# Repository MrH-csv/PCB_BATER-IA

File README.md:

# BATER-IA_PCB
Kicad files for the PCB design.

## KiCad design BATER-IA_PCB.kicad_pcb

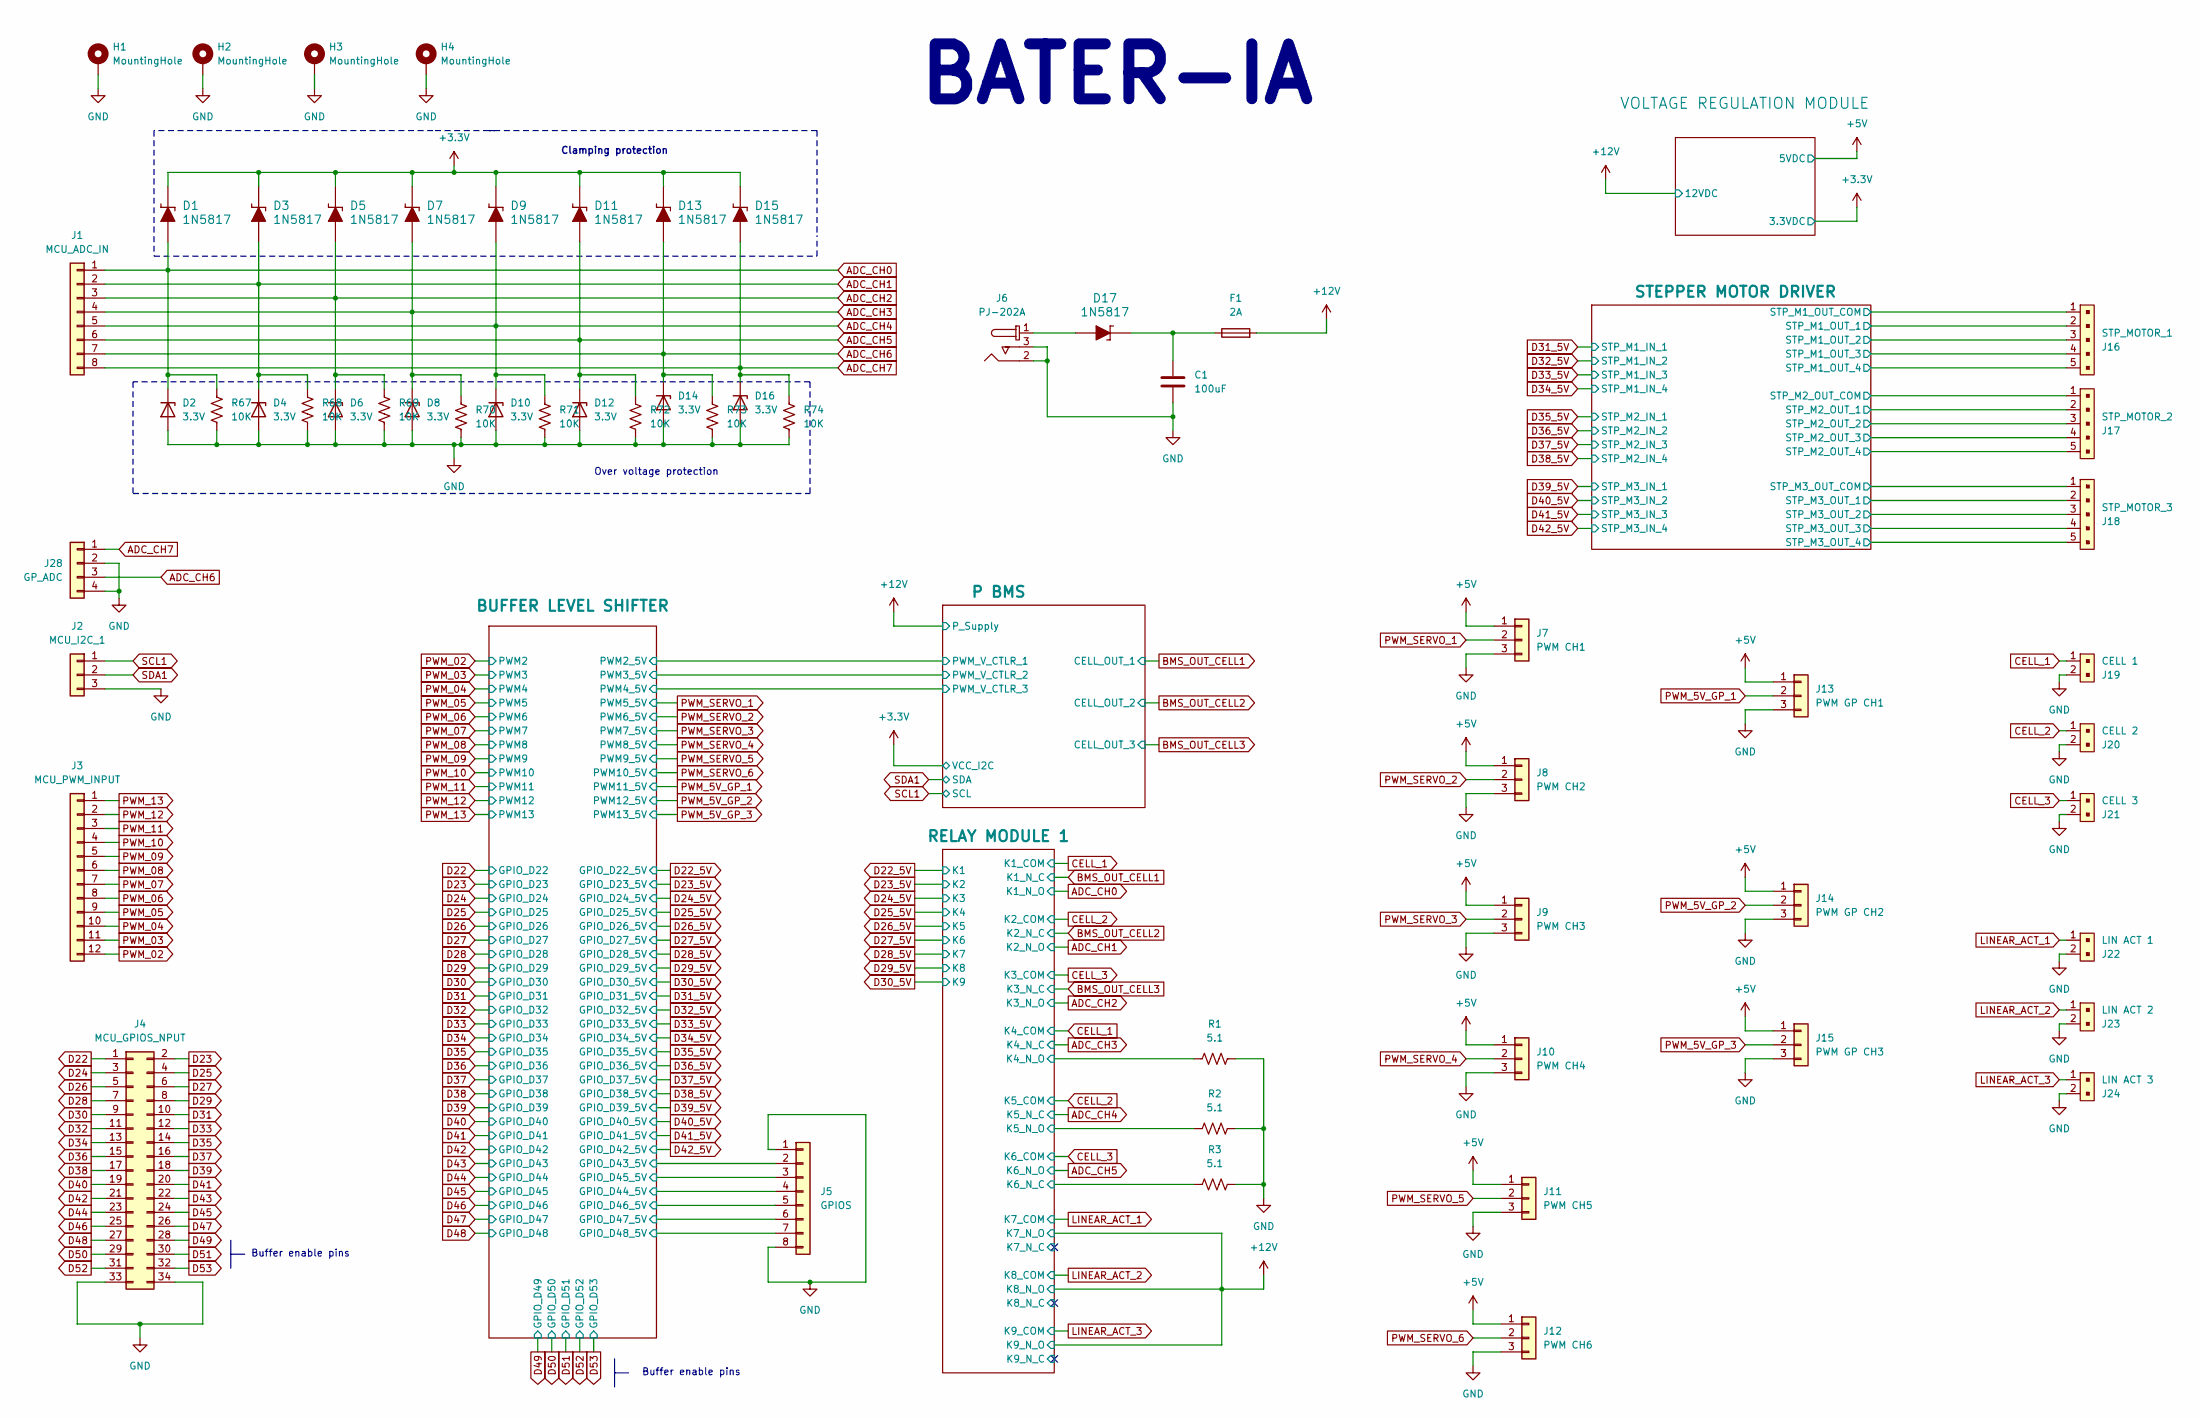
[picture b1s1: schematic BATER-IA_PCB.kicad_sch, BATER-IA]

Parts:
C1: 100uF; CP_Radial_D8.0mm_P5.00mm
D1, D3, D5, D7, D9, D11, D13, D15, D17: 1N5817; D_DO-41_SOD81_P9.20mm_Horizontal; MPN 1N5819; Digi-Key_PN 1N5819FSCT-ND
D2, D4, D6, D8, D10, D12, D14, D16: 3.3V; D_DO-35_SOD27_P10.16mm_Horizontal
F1: 2A; Fuseholder_Clip-5x20mm_Bel_FC-203-22_Lateral_P17.80x5.00mm_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
H1, H2, H3, H4: MountingHole; MountingHole_2.2mm_M2_DIN965_Pad_TopBottom
J1: MCU_ADC_IN; PinHeader_1x08_P2.54mm_Vertical
J2: MCU_I2C_1; PinHeader_1x03_P2.54mm_Vertical
J3: MCU_PWM_INPUT; PinHeader_1x12_P2.54mm_Vertical
J4: MCU_GPIOS_NPUT; PinHeader_2x17_P2.54mm_Vertical
J5: GPIOS; PinHeader_1x08_P2.54mm_Vertical
J6: PJ-202A; BarrelJack_Horizontal; MPN PJ-202A; Digi-Key_PN CP-202A-ND
J7: PWM CH1; PinHeader_1x03_P2.54mm_Vertical
J8: PWM CH2; PinHeader_1x03_P2.54mm_Vertical
J9: PWM CH3; PinHeader_1x03_P2.54mm_Vertical
J10: PWM CH4; PinHeader_1x03_P2.54mm_Vertical
J11: PWM CH5; PinHeader_1x03_P2.54mm_Vertical
J12: PWM CH6; PinHeader_1x03_P2.54mm_Vertical
J13: PWM GP CH1; PinHeader_1x03_P2.54mm_Vertical
J14: PWM GP CH2; PinHeader_1x03_P2.54mm_Vertical
J15: PWM GP CH3; PinHeader_1x03_P2.54mm_Vertical
J16: STP_MOTOR_1; PinHeader_1x5_P2.5mm_Drill1.1mm; MPN B5B-XH-A(LF)(SN); Digi-Key_PN 455-2270-ND
J17: STP_MOTOR_2; PinHeader_1x5_P2.5mm_Drill1.1mm; MPN B5B-XH-A(LF)(SN); Digi-Key_PN 455-2270-ND
J18: STP_MOTOR_3; PinHeader_1x5_P2.5mm_Drill1.1mm; MPN B5B-XH-A(LF)(SN); Digi-Key_PN 455-2270-ND
J19: CELL 1; PinHeader_1x2_P2.5mm_Drill1.1mm; MPN B2B-XH-A(LF)(SN); Digi-Key_PN 455-2247-ND
J20: CELL 2; PinHeader_1x2_P2.5mm_Drill1.1mm; MPN B2B-XH-A(LF)(SN); Digi-Key_PN 455-2247-ND
J21: CELL 3; PinHeader_1x2_P2.5mm_Drill1.1mm; MPN B2B-XH-A(LF)(SN); Digi-Key_PN 455-2247-ND
J22: LIN ACT 1; PinHeader_1x2_P2.5mm_Drill1.1mm; MPN B2B-XH-A(LF)(SN); Digi-Key_PN 455-2247-ND
J23: LIN ACT 2; PinHeader_1x2_P2.5mm_Drill1.1mm; MPN B2B-XH-A(LF)(SN); Digi-Key_PN 455-2247-ND
J24: LIN ACT 3; PinHeader_1x2_P2.5mm_Drill1.1mm; MPN B2B-XH-A(LF)(SN); Digi-Key_PN 455-2247-ND
J28: GP_ADC; PinHeader_1x04_P2.54mm_Vertical
R1, R2, R3: 5.1; R_Axial_DIN0614_L14.3mm_D5.7mm_P15.24mm_Horizontal
R67, R68, R69, R70, R71, R72, R73, R74: 10K; R_Axial_DIN0207_L6.3mm_D2.5mm_P7.62mm_Horizontal

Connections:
+3.3V: D1.K, D3.K, D5.K, D7.K, D9.K, D11.K, D13.K, D15.K; also elsewhere on the board
+5V: J7.1, J8.1, J9.1, J10.1, J11.1, J12.1, J13.1, J14.1, J15.1, J16.1, J17.1, J18.1; also elsewhere on the board
+12V: F1.2; also elsewhere on the board
/BUFFER LEVEL SHIFTER/GPIO_D43_5V: J5.2; also elsewhere on the board
/BUFFER LEVEL SHIFTER/GPIO_D44_5V: J5.4; also elsewhere on the board
/BUFFER LEVEL SHIFTER/GPIO_D45_5V: J5.3; also elsewhere on the board
/BUFFER LEVEL SHIFTER/GPIO_D46_5V: J5.5; also elsewhere on the board
/BUFFER LEVEL SHIFTER/GPIO_D47_5V: J5.6; also elsewhere on the board
/BUFFER LEVEL SHIFTER/GPIO_D48_5V: J5.7; also elsewhere on the board
/RELAY MODULE 1/K4_N_O: R1.1; also elsewhere on the board
/RELAY MODULE 1/K5_N_O: R2.1; also elsewhere on the board
/RELAY MODULE 1/K6_N_C: R3.1; also elsewhere on the board
/STEPPER MOTOR DRIVER/STP_M1_OUT_1: J16.2; also elsewhere on the board
/STEPPER MOTOR DRIVER/STP_M1_OUT_2: J16.3; also elsewhere on the board
/STEPPER MOTOR DRIVER/STP_M1_OUT_3: J16.4; also elsewhere on the board
/STEPPER MOTOR DRIVER/STP_M1_OUT_4: J16.5; also elsewhere on the board
/STEPPER MOTOR DRIVER/STP_M2_OUT_1: J17.2; also elsewhere on the board
/STEPPER MOTOR DRIVER/STP_M2_OUT_2: J17.3; also elsewhere on the board
/STEPPER MOTOR DRIVER/STP_M2_OUT_3: J17.4; also elsewhere on the board
/STEPPER MOTOR DRIVER/STP_M2_OUT_4: J17.5; also elsewhere on the board
/STEPPER MOTOR DRIVER/STP_M3_OUT_1: J18.2; also elsewhere on the board
/STEPPER MOTOR DRIVER/STP_M3_OUT_2: J18.3; also elsewhere on the board
/STEPPER MOTOR DRIVER/STP_M3_OUT_3: J18.4; also elsewhere on the board
/STEPPER MOTOR DRIVER/STP_M3_OUT_4: J18.5; also elsewhere on the board
ADC_CH0: D1.A, D2.1 (K), J1.1, R67.1; also elsewhere on the board
ADC_CH1: D3.A, D4.1 (K), J1.2, R68.1; also elsewhere on the board
ADC_CH2: D5.A, D6.1 (K), J1.3, R69.1; also elsewhere on the board
ADC_CH3: D7.A, D8.1 (K), J1.4, R70.1; also elsewhere on the board
ADC_CH4: D9.A, D10.1 (K), J1.5, R71.1; also elsewhere on the board
ADC_CH5: D11.A, D12.1 (K), J1.6, R72.1; also elsewhere on the board
ADC_CH6: D13.A, D14.1 (K), J1.7, J28.3, R73.1
ADC_CH7: D15.A, D16.1 (K), J1.8, J28.1, R74.1
CELL_1: J19.1; also elsewhere on the board
CELL_2: J20.1; also elsewhere on the board
CELL_3: J21.1; also elsewhere on the board
D22: J4.1; also elsewhere on the board
D23: J4.2; also elsewhere on the board
D24: J4.3; also elsewhere on the board
D25: J4.4; also elsewhere on the board
D26: J4.5; also elsewhere on the board
D27: J4.6; also elsewhere on the board
D28: J4.7; also elsewhere on the board
D29: J4.8; also elsewhere on the board
D30: J4.9; also elsewhere on the board
D31: J4.10; also elsewhere on the board
D32: J4.11; also elsewhere on the board
D33: J4.12; also elsewhere on the board
D34: J4.13; also elsewhere on the board
D35: J4.14; also elsewhere on the board
D36: J4.15; also elsewhere on the board
D37: J4.16; also elsewhere on the board
D38: J4.17; also elsewhere on the board
D39: J4.18; also elsewhere on the board
D40: J4.19; also elsewhere on the board
D41: J4.20; also elsewhere on the board
D42: J4.21; also elsewhere on the board
D43: J4.22; also elsewhere on the board
D44: J4.23; also elsewhere on the board
D45: J4.24; also elsewhere on the board
D46: J4.25; also elsewhere on the board
D47: J4.26; also elsewhere on the board
D48: J4.27; also elsewhere on the board
D49: J4.28; also elsewhere on the board
D50: J4.29; also elsewhere on the board
D51: J4.30; also elsewhere on the board
D52: J4.31; also elsewhere on the board
D53: J4.32; also elsewhere on the board
GND: C1.2, D2.2 (A), D4.2 (A), D6.2 (A), D8.2 (A), D10.2 (A), D12.2 (A), D14.2 (A), D16.2 (A), H1.1, H2.1, H3.1, H4.1, J2.3, J4.33, J4.34, J5.1, J5.8, J6.2, J6.3, J7.3, J8.3, J9.3, J10.3, J11.3, J12.3, J13.3, J14.3, J15.3, J19.2, J20.2, J21.2, J22.2, J23.2, J24.2, J28.2, J28.4, R1.2, R2.2, R3.2, R67.2, R68.2, R69.2, R70.2, R71.2, R72.2, R73.2, R74.2; also elsewhere on the board
LINEAR_ACT_1: J22.1; also elsewhere on the board
LINEAR_ACT_2: J23.1; also elsewhere on the board
LINEAR_ACT_3: J24.1; also elsewhere on the board
unnamed: C1.1, D17.K, F1.1
unnamed: D17.A, J6.1
PWM_02: J3.12; also elsewhere on the board
PWM_03: J3.11; also elsewhere on the board
PWM_04: J3.10; also elsewhere on the board
PWM_05: J3.9; also elsewhere on the board
PWM_5V_GP_1: J13.2; also elsewhere on the board
PWM_5V_GP_2: J14.2; also elsewhere on the board
PWM_5V_GP_3: J15.2; also elsewhere on the board
PWM_06: J3.8; also elsewhere on the board
PWM_07: J3.7; also elsewhere on the board
PWM_08: J3.6; also elsewhere on the board
PWM_09: J3.5; also elsewhere on the board
PWM_10: J3.4; also elsewhere on the board
PWM_11: J3.3; also elsewhere on the board
PWM_12: J3.2; also elsewhere on the board
PWM_13: J3.1; also elsewhere on the board
PWM_SERVO_1: J7.2; also elsewhere on the board
PWM_SERVO_2: J8.2; also elsewhere on the board
PWM_SERVO_3: J9.2; also elsewhere on the board
PWM_SERVO_4: J10.2; also elsewhere on the board
PWM_SERVO_5: J11.2; also elsewhere on the board
PWM_SERVO_6: J12.2; also elsewhere on the board
SCL1: J2.1; also elsewhere on the board
SDA1: J2.2; also elsewhere on the board

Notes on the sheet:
Over voltage protection
Buffer enable pins
BATER-IA
Clamping protection

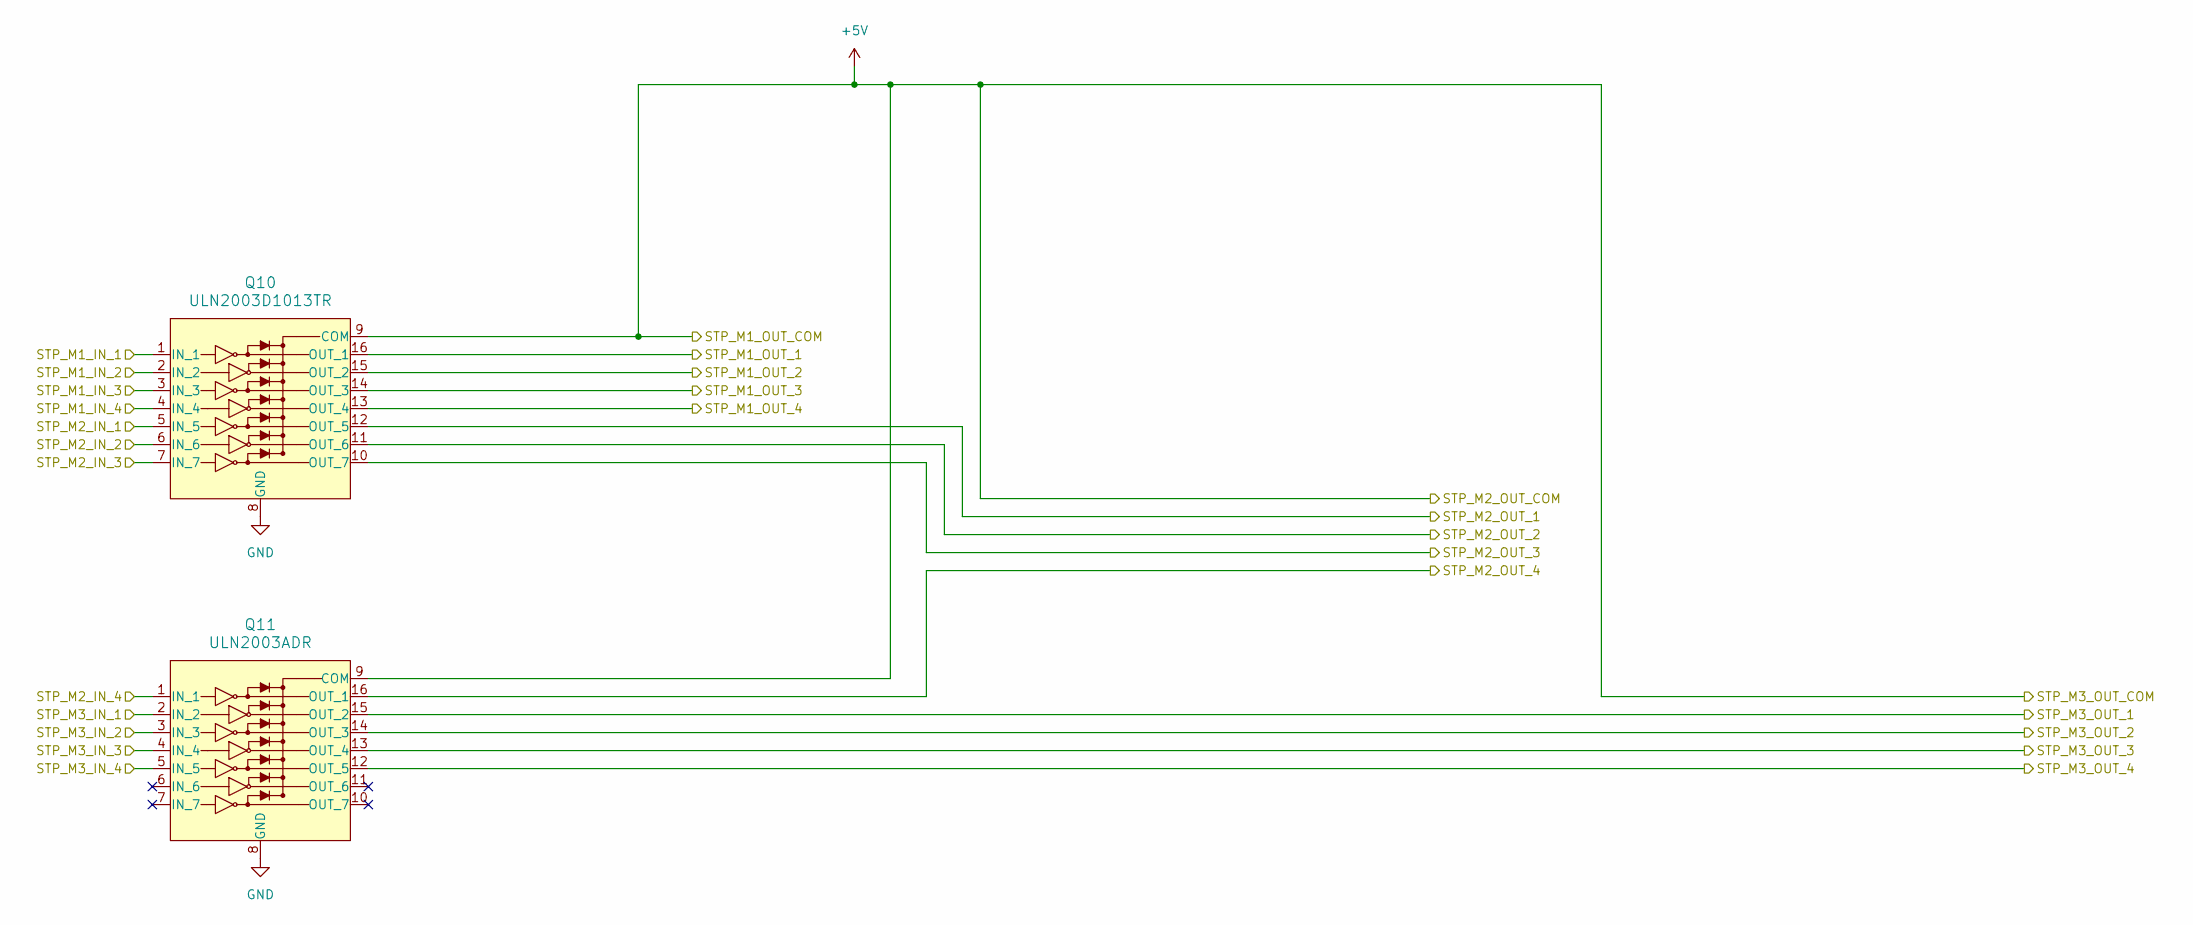
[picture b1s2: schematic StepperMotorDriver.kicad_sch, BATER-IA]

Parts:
Q10: ULN2003D1013TR; SOIC-16_W3.90mm; MPN ULN2003D1013TR; Digi-Key_PN 497-2345-1-ND
Q11: ULN2003ADR; SOIC-16_W3.90mm; MPN ULN2003ADR; Digi-Key_PN 296-1368-1-ND

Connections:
+5V: Q10.9 (COM), Q11.9 (COM); also elsewhere on the board
/STEPPER MOTOR DRIVER/STP_M1_OUT_1: Q10.16 (OUT_1); also elsewhere on the board
/STEPPER MOTOR DRIVER/STP_M1_OUT_2: Q10.15 (OUT_2); also elsewhere on the board
/STEPPER MOTOR DRIVER/STP_M1_OUT_3: Q10.14 (OUT_3); also elsewhere on the board
/STEPPER MOTOR DRIVER/STP_M1_OUT_4: Q10.13 (OUT_4); also elsewhere on the board
/STEPPER MOTOR DRIVER/STP_M2_OUT_1: Q10.12 (OUT_5); also elsewhere on the board
/STEPPER MOTOR DRIVER/STP_M2_OUT_2: Q10.11 (OUT_6); also elsewhere on the board
/STEPPER MOTOR DRIVER/STP_M2_OUT_3: Q10.10 (OUT_7); also elsewhere on the board
/STEPPER MOTOR DRIVER/STP_M2_OUT_4: Q11.16 (OUT_1); also elsewhere on the board
/STEPPER MOTOR DRIVER/STP_M3_OUT_1: Q11.15 (OUT_2); also elsewhere on the board
/STEPPER MOTOR DRIVER/STP_M3_OUT_2: Q11.14 (OUT_3); also elsewhere on the board
/STEPPER MOTOR DRIVER/STP_M3_OUT_3: Q11.13 (OUT_4); also elsewhere on the board
/STEPPER MOTOR DRIVER/STP_M3_OUT_4: Q11.12 (OUT_5); also elsewhere on the board
D31_5V: Q10.1 (IN_1); also elsewhere on the board
D32_5V: Q10.2 (IN_2); also elsewhere on the board
D33_5V: Q10.3 (IN_3); also elsewhere on the board
D34_5V: Q10.4 (IN_4); also elsewhere on the board
D35_5V: Q10.5 (IN_5); also elsewhere on the board
D36_5V: Q10.6 (IN_6); also elsewhere on the board
D37_5V: Q10.7 (IN_7); also elsewhere on the board
D38_5V: Q11.1 (IN_1); also elsewhere on the board
D39_5V: Q11.2 (IN_2); also elsewhere on the board
D40_5V: Q11.3 (IN_3); also elsewhere on the board
D41_5V: Q11.4 (IN_4); also elsewhere on the board
D42_5V: Q11.5 (IN_5); also elsewhere on the board
GND: Q10.8 (GND), Q11.8 (GND); also elsewhere on the board

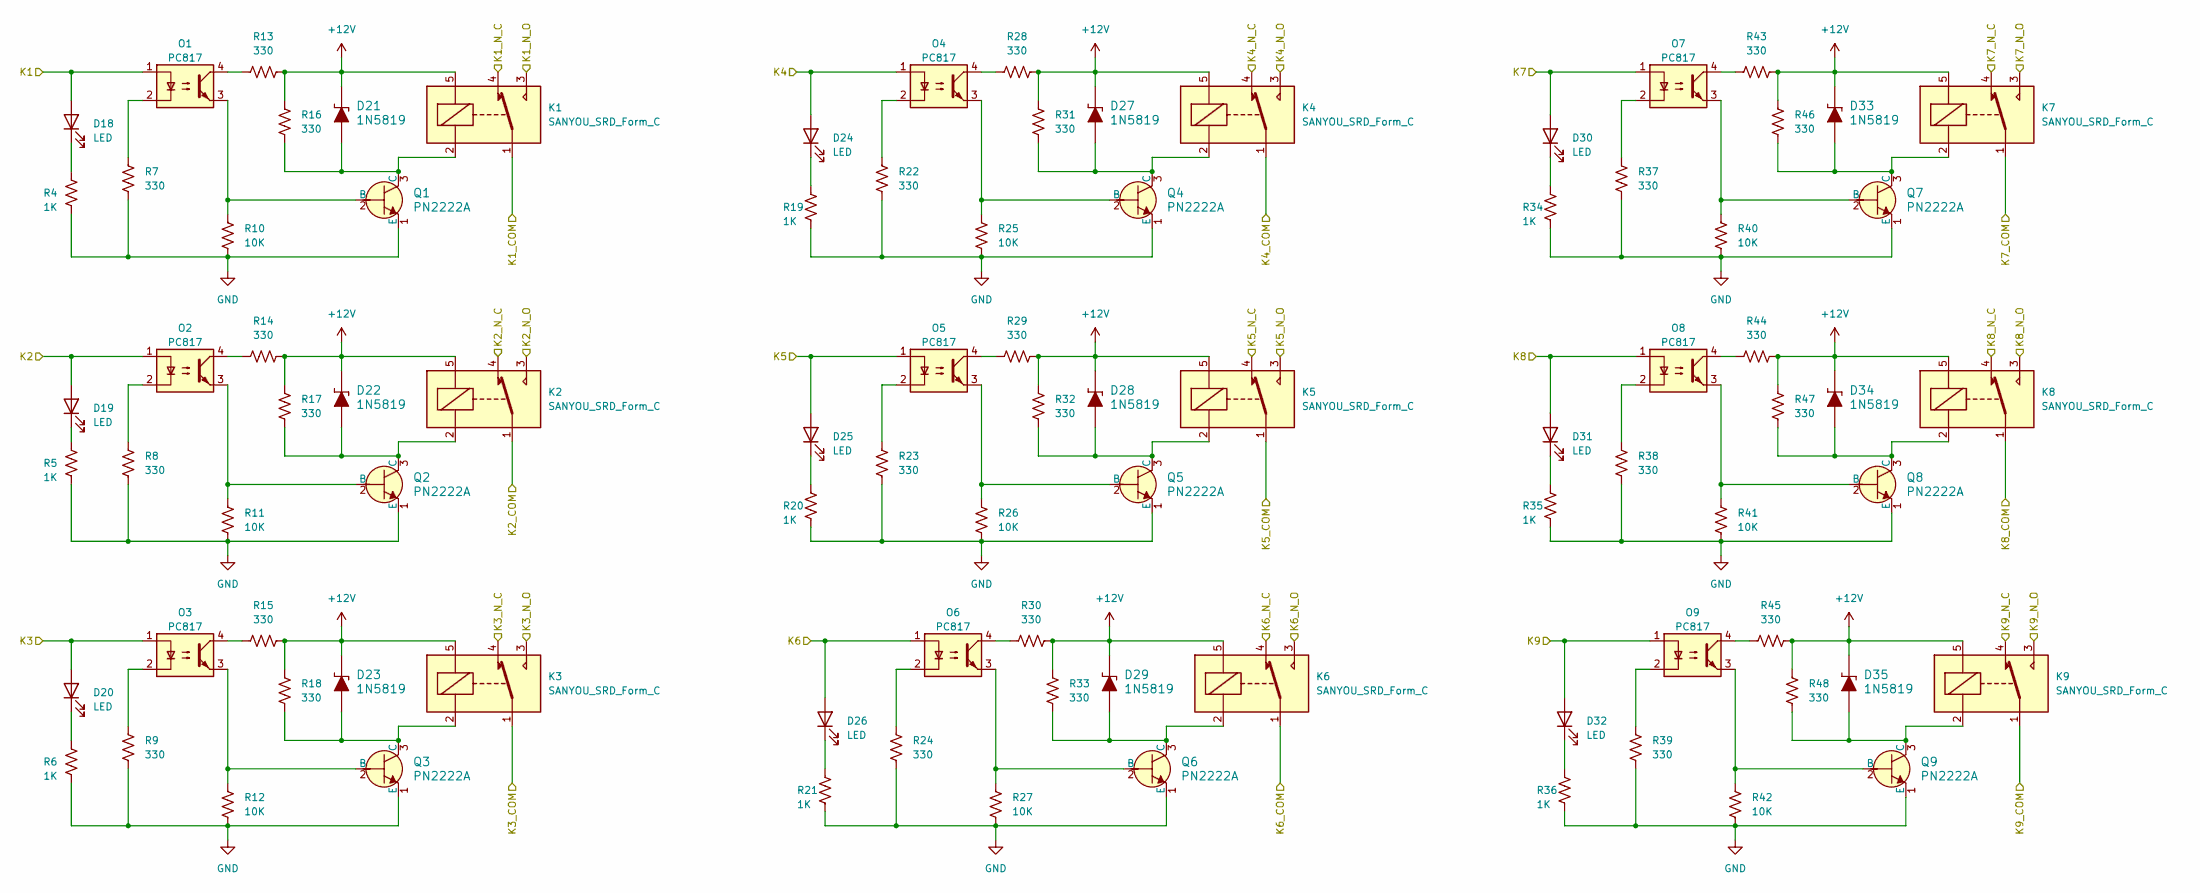
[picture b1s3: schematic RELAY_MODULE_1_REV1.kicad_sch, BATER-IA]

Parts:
D18, D19, D20, D24, D25, D26, D30, D31, D32: LED; LED_D3.0mm
D21, D22, D23, D27, D28, D29, D33, D34, D35: 1N5819; D_DO-41_SOD81_P9.20mm_Horizontal; MPN 1N5819; Digi-Key_PN 1N5819FSCT-ND
K1, K2, K3, K4, K5, K6, K7, K8, K9: SANYOU_SRD_Form_C; Relay_SPDT_SANYOU_SRD_Series_Form_C
O1, O2, O3, O4, O5, O6, O7, O8, O9: PC817; DIP-4_W7.62mm
Q1, Q2, Q3, Q4, Q5, Q6, Q7, Q8, Q9: PN2222A; TO-92_Inline; MPN PN2222A; Digi-Key_PN PN2222ACS-ND
R4, R5, R6, R19, R20, R21, R34, R35, R36: 1K; R_Axial_DIN0207_L6.3mm_D2.5mm_P7.62mm_Horizontal
R7, R8, R9, R13, R14, R15, R16, R17, R18, R22, R23, R24, R28, R29, R30, R31, R32, R33, R37, R38, R39, R43, R44, R45, R46, R47, R48: 330; R_Axial_DIN0207_L6.3mm_D2.5mm_P7.62mm_Horizontal
R10, R11, R12, R25, R26, R27, R40, R41, R42: 10K; R_Axial_DIN0207_L6.3mm_D2.5mm_P7.62mm_Horizontal

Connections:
+12V: D21.K, D22.K, D23.K, D27.K, D28.K, D29.K, D33.K, D34.K, D35.K, K1.5, K2.5, K3.5, K4.5, K5.5, K6.5, K7.3, K7.5, K8.3, K8.5, K9.3, K9.5, R13.2, R14.2, R15.2, R16.1, R17.1, R18.1, R28.2, R29.2, R30.2, R31.1, R32.1, R33.1, R43.2, R44.2, R45.2, R46.1, R47.1, R48.1; also elsewhere on the board
/RELAY MODULE 1/K4_N_O: K4.3; also elsewhere on the board
/RELAY MODULE 1/K5_N_O: K5.3; also elsewhere on the board
/RELAY MODULE 1/K6_N_C: K6.4; also elsewhere on the board
/RELAY MODULE 1/K7_N_C: K7.4
/RELAY MODULE 1/K8_N_C: K8.4
/RELAY MODULE 1/K9_N_C: K9.4
ADC_CH0: K1.3; also elsewhere on the board
ADC_CH1: K2.3; also elsewhere on the board
ADC_CH2: K3.3; also elsewhere on the board
ADC_CH3: K4.4; also elsewhere on the board
ADC_CH4: K5.4; also elsewhere on the board
ADC_CH5: K6.3; also elsewhere on the board
BMS_OUT_CELL1: K1.4; also elsewhere on the board
BMS_OUT_CELL2: K2.4; also elsewhere on the board
BMS_OUT_CELL3: K3.4; also elsewhere on the board
CELL_1: K1.1, K4.1; also elsewhere on the board
CELL_2: K2.1, K5.1; also elsewhere on the board
CELL_3: K3.1, K6.1; also elsewhere on the board
D22_5V: D18.2 (A), O1.1; also elsewhere on the board
D23_5V: D19.2 (A), O2.1; also elsewhere on the board
D24_5V: D20.2 (A), O3.1; also elsewhere on the board
D25_5V: D24.2 (A), O4.1; also elsewhere on the board
D26_5V: D25.2 (A), O5.1; also elsewhere on the board
D27_5V: D26.2 (A), O6.1; also elsewhere on the board
D28_5V: D30.2 (A), O7.1; also elsewhere on the board
D29_5V: D31.2 (A), O8.1; also elsewhere on the board
D30_5V: D32.2 (A), O9.1; also elsewhere on the board
GND: Q1.1 (E), Q2.1 (E), Q3.1 (E), Q4.1 (E), Q5.1 (E), Q6.1 (E), Q7.1 (E), Q8.1 (E), Q9.1 (E), R4.2, R5.2, R6.2, R7.2, R8.2, R9.2, R10.2, R11.2, R12.2, R19.2, R20.2, R21.2, R22.2, R23.2, R24.2, R25.2, R26.2, R27.2, R34.2, R35.2, R36.2, R37.2, R38.2, R39.2, R40.2, R41.2, R42.2; also elsewhere on the board
LINEAR_ACT_1: K7.1; also elsewhere on the board
LINEAR_ACT_2: K8.1; also elsewhere on the board
LINEAR_ACT_3: K9.1; also elsewhere on the board
unnamed: D18.1 (K), R4.1
unnamed: D19.1 (K), R5.1
unnamed: D20.1 (K), R6.1
unnamed: D24.1 (K), R19.1
unnamed: D25.1 (K), R20.1
unnamed: D26.1 (K), R21.1
unnamed: D30.1 (K), R34.1
unnamed: D31.1 (K), R35.1
unnamed: D32.1 (K), R36.1
unnamed: O1.2, R7.1
unnamed: O1.4, R13.1
unnamed: O2.2, R8.1
unnamed: O2.4, R14.1
unnamed: O3.2, R9.1
unnamed: O3.4, R15.1
unnamed: O4.2, R22.1
unnamed: O4.4, R28.1
unnamed: O5.2, R23.1
unnamed: O5.4, R29.1
unnamed: O6.2, R24.1
unnamed: O6.4, R30.1
unnamed: O7.2, R37.1
unnamed: O7.4, R43.1
unnamed: O8.2, R38.1
unnamed: O8.4, R44.1
unnamed: O9.2, R39.1
unnamed: O9.4, R45.1
unnamed: O1.3, Q1.2 (B), R10.1
unnamed: D21.A, K1.2, Q1.3 (C), R16.2
unnamed: O2.3, Q2.2 (B), R11.1
unnamed: D22.A, K2.2, Q2.3 (C), R17.2
unnamed: O3.3, Q3.2 (B), R12.1
unnamed: D23.A, K3.2, Q3.3 (C), R18.2
unnamed: O4.3, Q4.2 (B), R25.1
unnamed: D27.A, K4.2, Q4.3 (C), R31.2
unnamed: O5.3, Q5.2 (B), R26.1
unnamed: D28.A, K5.2, Q5.3 (C), R32.2
unnamed: O6.3, Q6.2 (B), R27.1
unnamed: D29.A, K6.2, Q6.3 (C), R33.2
unnamed: O7.3, Q7.2 (B), R40.1
unnamed: D33.A, K7.2, Q7.3 (C), R46.2
unnamed: O8.3, Q8.2 (B), R41.1
unnamed: D34.A, K8.2, Q8.3 (C), R47.2
unnamed: O9.3, Q9.2 (B), R42.1
unnamed: D35.A, K9.2, Q9.3 (C), R48.2

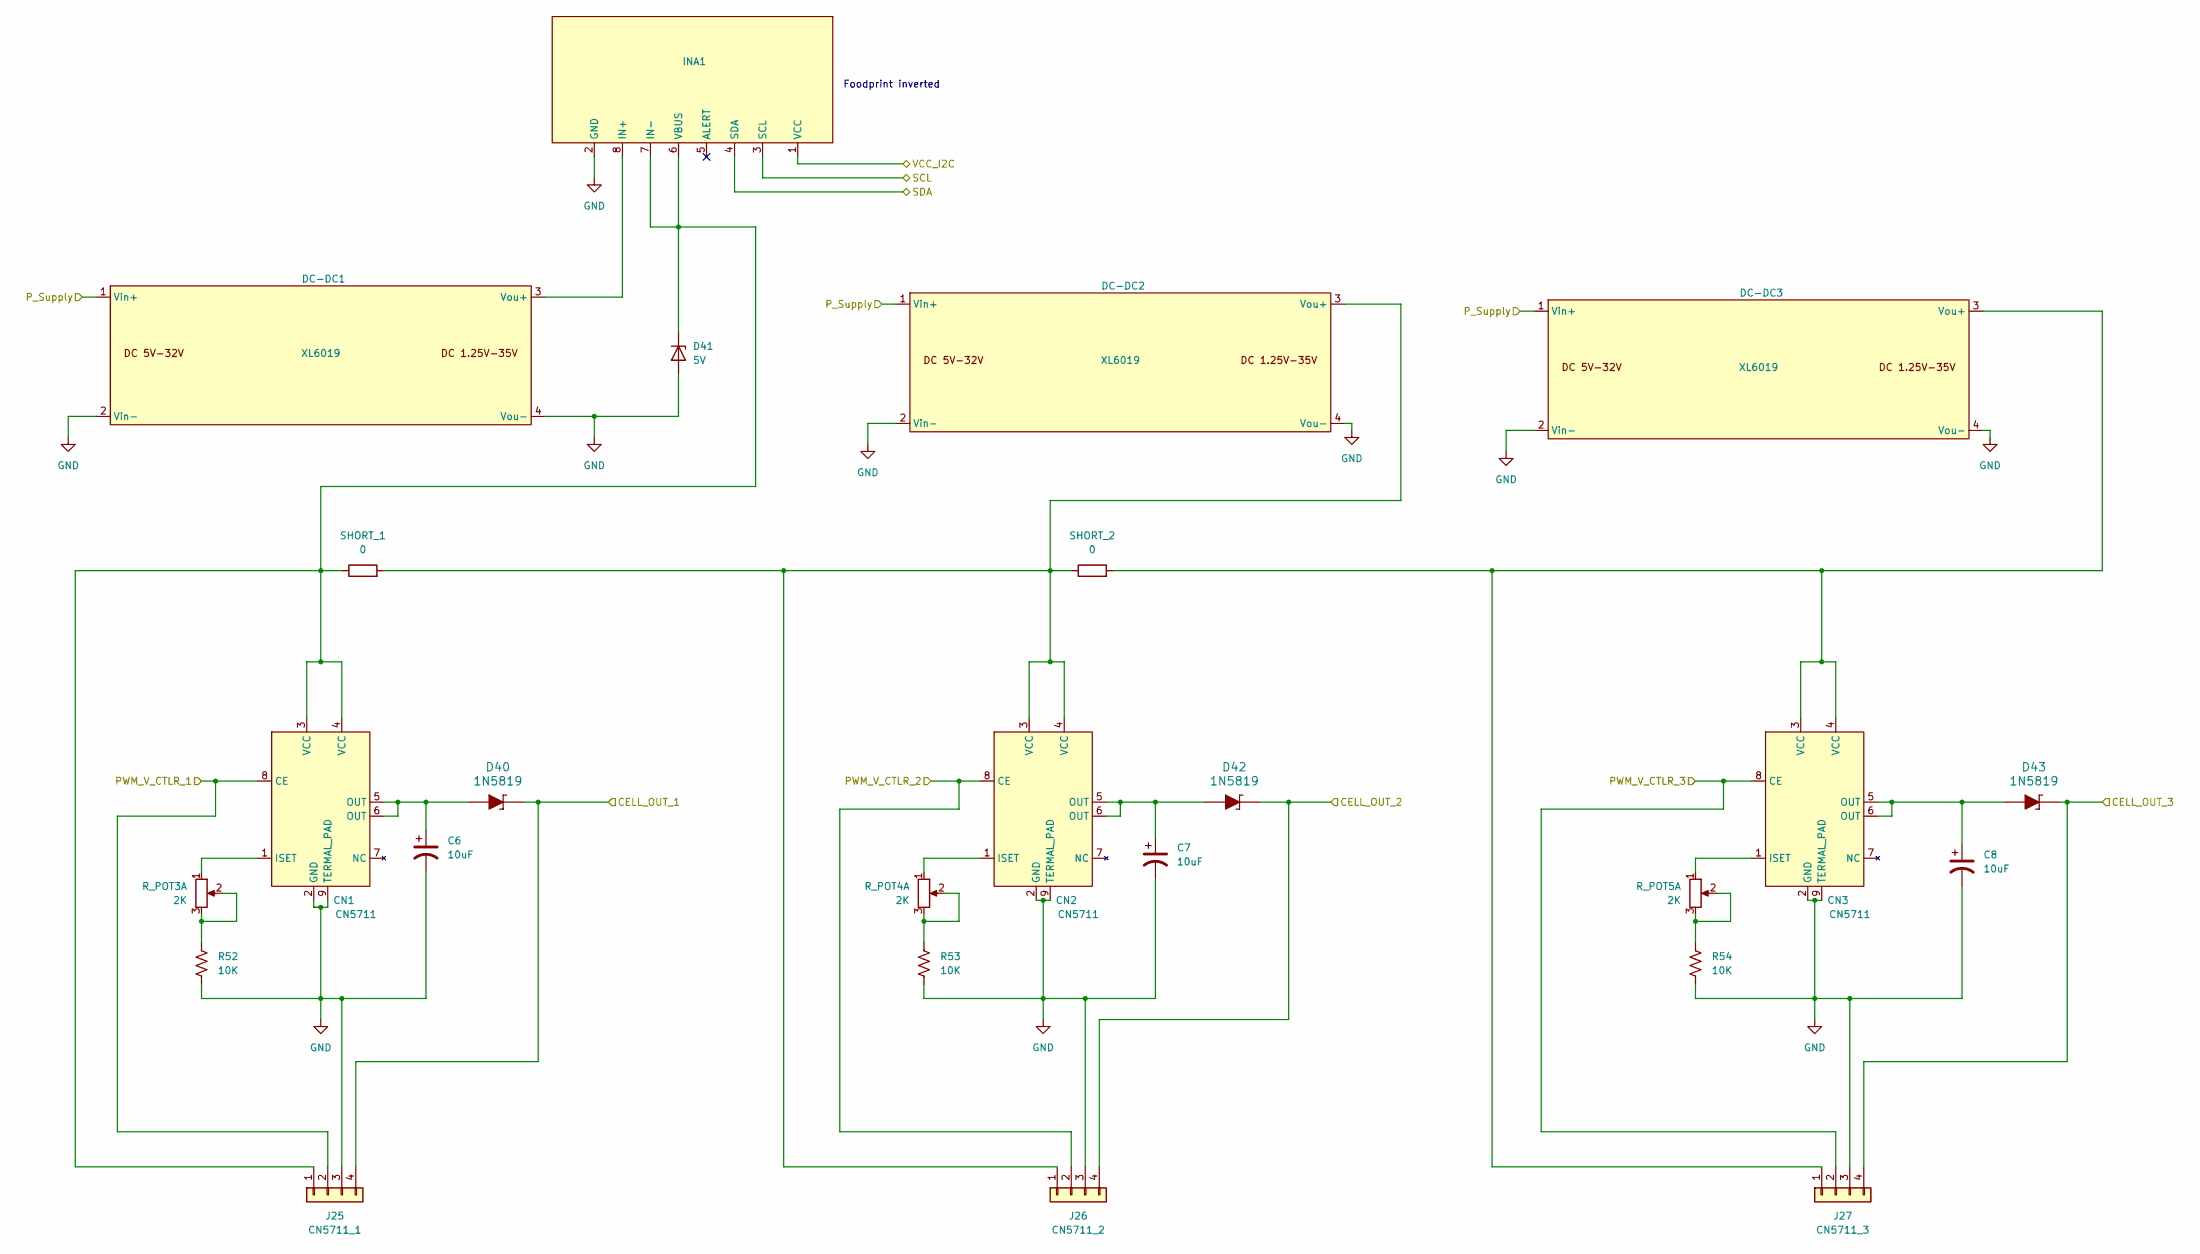
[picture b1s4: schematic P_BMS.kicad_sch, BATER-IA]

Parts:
C6, C7, C8: 10uF; C_Radial_D5.0mm_H11.0mm_P2.00mm
CN1, CN2, CN3: CN5711; Texas_HSOP-8-1EP_3.9x4.9mm_P1.27mm_ThermalVias
D40, D42, D43: 1N5819; D_DO-41_SOD81_P9.20mm_Horizontal; MPN 1N5819; Digi-Key_PN 1N5819FSCT-ND
D41: 5V; D_DO-35_SOD27_P10.16mm_Horizontal
DC-DC1, DC-DC2, DC-DC3: XL6019; XL6019 MODULE
INA1: INA226; INA226 Module
J25: CN5711_1; PinSocket_1x04_P2.54mm_Vertical
J26: CN5711_2; PinSocket_1x04_P2.54mm_Vertical
J27: CN5711_3; PinSocket_1x04_P2.54mm_Vertical
R52, R53, R54: 10K; R_Axial_DIN0207_L6.3mm_D2.5mm_P7.62mm_Horizontal
R_POT3, R_POT4, R_POT5: 2K; Potentiometer_Bourns_3296W_Vertical
SHORT_1, SHORT_2: 0; Short_5.08mm_Drill1.3mm

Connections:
+3.3V: INA1.1 (VCC); also elsewhere on the board
+12V: DC-DC1.1 (Vin+), DC-DC2.1 (Vin+), DC-DC3.1 (Vin+); also elsewhere on the board
/BUFFER LEVEL SHIFTER/PWM2_5V: CN1.8 (CE), J25.2; also elsewhere on the board
/BUFFER LEVEL SHIFTER/PWM3_5V: CN2.8 (CE), J26.2; also elsewhere on the board
/BUFFER LEVEL SHIFTER/PWM4_5V: CN3.8 (CE), J27.2; also elsewhere on the board
BMS_OUT_CELL1: D40.K, J25.4; also elsewhere on the board
BMS_OUT_CELL2: D42.K, J26.4; also elsewhere on the board
BMS_OUT_CELL3: D43.K, J27.4; also elsewhere on the board
GND: C6.2, C7.2, C8.2, CN1.2 (GND), CN1.9 (TERMAL_PAD), CN2.2 (GND), CN2.9 (TERMAL_PAD), CN3.2 (GND), CN3.9 (TERMAL_PAD), D41.2 (A), DC-DC1.2 (Vin-), DC-DC1.4 (Vou-), DC-DC2.2 (Vin-), DC-DC2.4 (Vou-), DC-DC3.2 (Vin-), DC-DC3.4 (Vou-), INA1.2 (GND), J25.3, J26.3, J27.3, R52.2, R53.2, R54.2; also elsewhere on the board
unnamed: C6.1, CN1.5 (OUT), CN1.6 (OUT), D40.A
unnamed: C7.1, CN2.5 (OUT), CN2.6 (OUT), D42.A
unnamed: C8.1, CN3.5 (OUT), CN3.6 (OUT), D43.A
unnamed: CN1.1 (ISET), R_POT3.1
unnamed: CN2.1 (ISET), R_POT4.1
unnamed: CN3.1 (ISET), R_POT5.1
unnamed: CN1.3 (VCC), CN1.4 (VCC), D41.1 (K), INA1.6 (VBUS), INA1.7 (IN-), J25.1, SHORT_1.1
unnamed: DC-DC1.3 (Vou+), INA1.8 (IN+)
unnamed: CN2.3 (VCC), CN2.4 (VCC), DC-DC2.3 (Vou+), J26.1, SHORT_1.2, SHORT_2.1
unnamed: CN3.3 (VCC), CN3.4 (VCC), DC-DC3.3 (Vou+), J27.1, SHORT_2.2
unnamed: R52.1, R_POT3.2, R_POT3.3
unnamed: R53.1, R_POT4.2, R_POT4.3
unnamed: R54.1, R_POT5.2, R_POT5.3
SCL1: INA1.3 (SCL); also elsewhere on the board
SDA1: INA1.4 (SDA); also elsewhere on the board

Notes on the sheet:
Foodprint inverted
